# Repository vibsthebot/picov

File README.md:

# picov

A RP2040 powered Pico formfactor devboard using usb-c. It includes a 4x4 2020 neopixel array. The pcb was designed in KiCad.

## Schematic

## PCB

## PCB back art (designed in Figma!)

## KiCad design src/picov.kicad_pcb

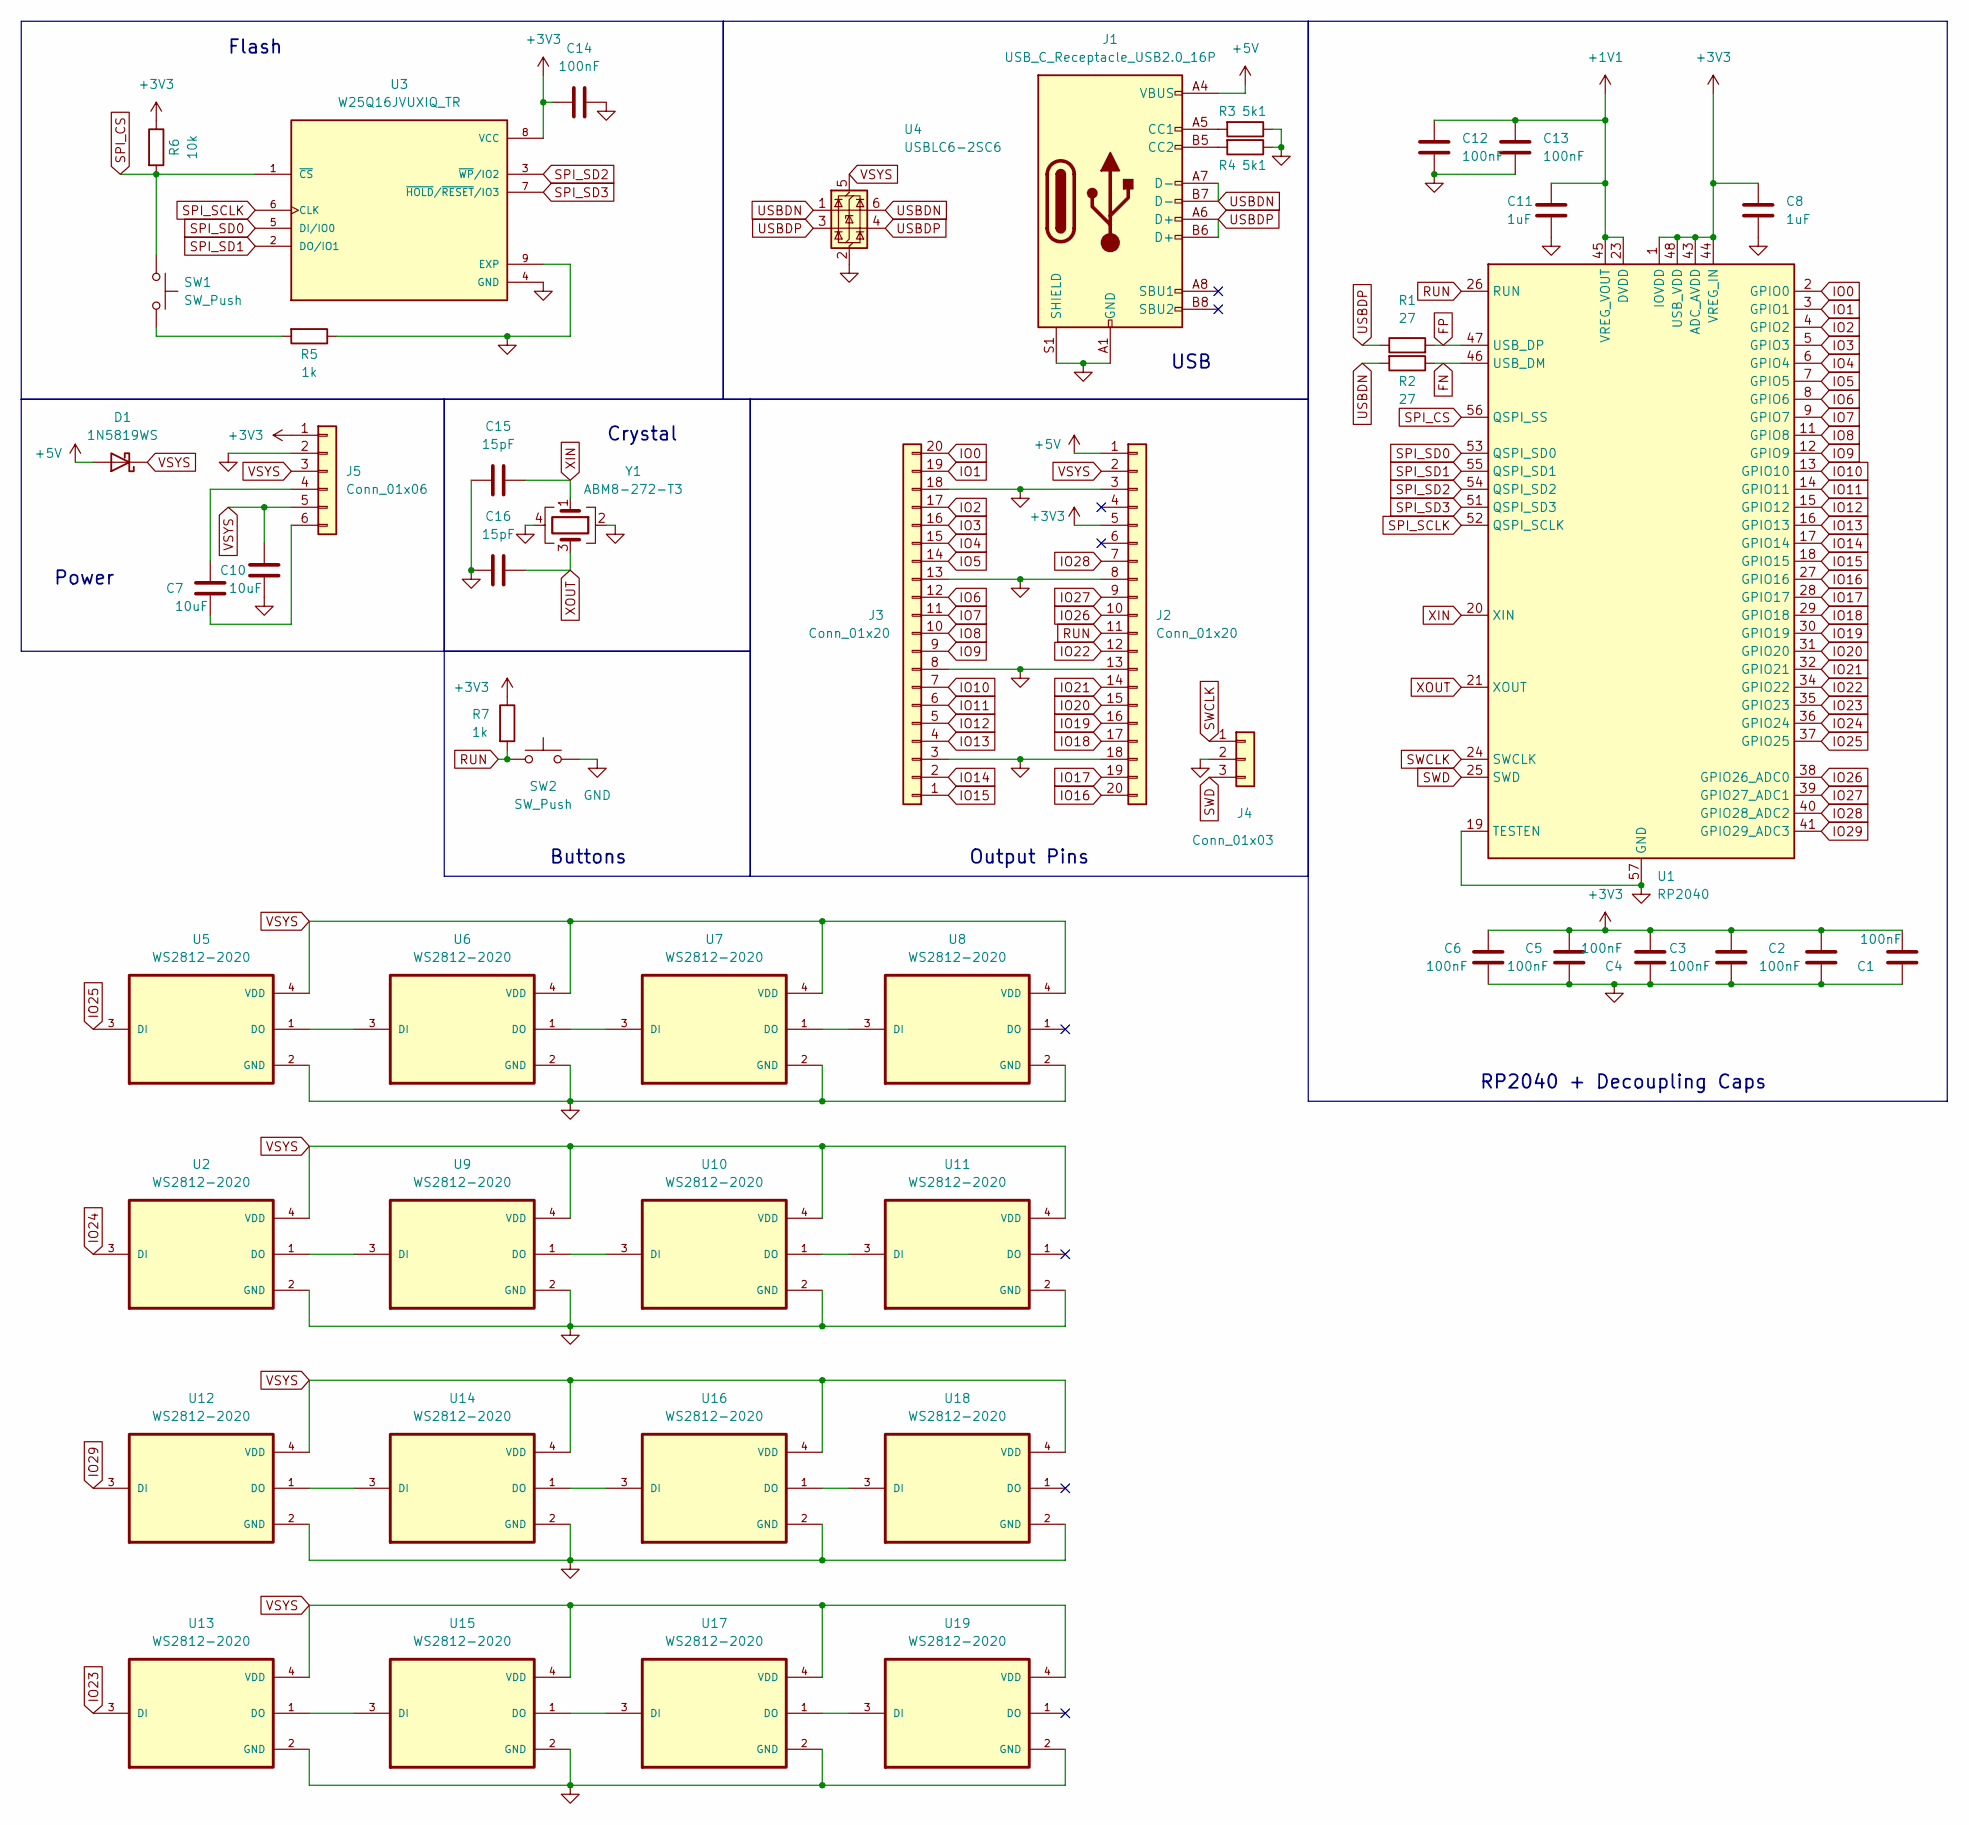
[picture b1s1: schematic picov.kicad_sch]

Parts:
C1, C2, C3, C4, C5, C6, C12, C13, C14: 100nF; C_0402_1005Metric; LCSC C1525
C7, C10: 10uF; C_0402_1005Metric; LCSC C15525
C8, C11: 1uF; C_0402_1005Metric; LCSC C52923
C15, C16: 15pF; C_0402_1005Metric; LCSC C1548
D1: 1N5819WS; D_SOD-123; LCSC C191023
J1: USB_C_Receptacle_USB2.0_16P; USB_C_Receptacle_G-Switch_GT-USB-7010ASV; LCSC C67380
J2, J3: Conn_01x20; PinHeader_1x20_P2.54mm_Vertical
J4: Conn_01x03; PinHeader_1x03_P2.54mm_Vertical
J5: Conn_01x06; SOT-23-6; LCSC C610271
R1, R2: 27; R_0402_1005Metric; LCSC C25100
R3, R4: 5k1; R_0402_1005Metric; LCSC C25905
R5, R7: 1k; R_0402_1005Metric; LCSC C11702
R6: 10k; R_0402_1005Metric; LCSC C25744
SW1, SW2: SW_Push; SMD_3x4; LCSC C455280
U1: RP2040; QFN-56-1EP_7x7mm_P0.4mm_EP3.2x3.2mm; LCSC C2040
U2, U5, U6, U7, U8, U9, U10, U11, U12, U13, U14, U15, U16, U17, U18, U19: WS2812-2020; LED_WS2812-2020; PARTREV V1.3; LCSC C26159668
U3: W25Q16JVUXIQ_TR; Winbond_USON-8-1EP_3x2mm_P0.5mm_EP0.2x1.6mm; PARTREV H; LCSC C2843335
U4: USBLC6-2SC6; SOT-23-6; LCSC C5180249
Y1: ABM8-272-T3; Crystal_SMD_3225-4Pin_3.2x2.5mm; LCSC C9002

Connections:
+1V1: C11.1, C12.1, C13.1, U1.23 (DVDD), U1.45 (VREG_VOUT), U1.50 (DVDD)
+3V3: C1.2, C2.2, C3.2, C4.2, C5.2, C6.2, C8.1, C14.1, J2.5, J5.1, R6.1, R7.1, U1.1 (IOVDD), U1.10 (IOVDD), U1.22 (IOVDD), U1.33 (IOVDD), U1.42 (IOVDD), U1.43 (ADC_AVDD), U1.44 (VREG_IN), U1.48 (USB_VDD), U1.49 (IOVDD), U3.8 (VCC)
+5V: D1.2 (A), J1.A4 (VBUS), J1.A9 (VBUS), J1.B4 (VBUS), J1.B9 (VBUS), J2.1
FN: R2.1, U1.46 (USB_DM)
FP: R1.2, U1.47 (USB_DP)
GND: C1.1, C2.1, C3.1, C4.1, C5.1, C6.1, C8.2, C10.2, C11.2, C12.2, C13.2, C14.2, C15.1, C16.1, J1.A1 (GND), J1.A12 (GND), J1.B1 (GND), J1.B12 (GND), J1.S1 (SHIELD), J2.3, J2.8, J2.13, J2.18, J3.3, J3.8, J3.13, J3.18, J4.2, J5.2, R3.1, R4.1, R5.1, SW2.2, U1.19 (TESTEN), U1.57 (GND), U2.2 (GND), U3.4 (GND), U3.9 (EXP), U4.2 (GND), U5.2 (GND), U6.2 (GND), U7.2 (GND), U8.2 (GND), U9.2 (GND), U10.2 (GND), U11.2 (GND), U12.2 (GND), U13.2 (GND), U14.2 (GND), U15.2 (GND), U16.2 (GND), U17.2 (GND), U18.2 (GND), U19.2 (GND), Y1.2, Y1.4
IO0: J3.20, U1.2 (GPIO0)
IO1: J3.19, U1.3 (GPIO1)
IO2: J3.17, U1.4 (GPIO2)
IO3: J3.16, U1.5 (GPIO3)
IO4: J3.15, U1.6 (GPIO4)
IO5: J3.14, U1.7 (GPIO5)
IO6: J3.12, U1.8 (GPIO6)
IO7: J3.11, U1.9 (GPIO7)
IO8: J3.10, U1.11 (GPIO8)
IO9: J3.9, U1.12 (GPIO9)
IO10: J3.7, U1.13 (GPIO10)
IO11: J3.6, U1.14 (GPIO11)
IO12: J3.5, U1.15 (GPIO12)
IO13: J3.4, U1.16 (GPIO13)
IO14: J3.2, U1.17 (GPIO14)
IO15: J3.1, U1.18 (GPIO15)
IO16: J2.20, U1.27 (GPIO16)
IO17: J2.19, U1.28 (GPIO17)
IO18: J2.17, U1.29 (GPIO18)
IO19: J2.16, U1.30 (GPIO19)
IO20: J2.15, U1.31 (GPIO20)
IO21: J2.14, U1.32 (GPIO21)
IO22: J2.12, U1.34 (GPIO22)
IO23: U1.35 (GPIO23), U13.3 (DI)
IO24: U1.36 (GPIO24), U2.3 (DI)
IO25: U1.37 (GPIO25), U5.3 (DI)
IO26: J2.10, U1.38 (GPIO26_ADC0)
IO27: J2.9, U1.39 (GPIO27_ADC1)
IO28: J2.7, U1.40 (GPIO28_ADC2)
IO29: U1.41 (GPIO29_ADC3), U12.3 (DI)
unnamed: J1.A5 (CC1), R3.2
unnamed: J1.B5 (CC2), R4.2
unnamed: C7.1, J5.4
unnamed: C7.2, J5.6
unnamed: R5.2, SW1.2
unnamed: U2.1 (DO), U9.3 (DI)
unnamed: U5.1 (DO), U6.3 (DI)
unnamed: U6.1 (DO), U7.3 (DI)
unnamed: U7.1 (DO), U8.3 (DI)
unnamed: U9.1 (DO), U10.3 (DI)
unnamed: U10.1 (DO), U11.3 (DI)
unnamed: U12.1 (DO), U14.3 (DI)
unnamed: U13.1 (DO), U15.3 (DI)
unnamed: U14.1 (DO), U16.3 (DI)
unnamed: U15.1 (DO), U17.3 (DI)
unnamed: U16.1 (DO), U18.3 (DI)
unnamed: U17.1 (DO), U19.3 (DI)
RUN: J2.11, R7.2, SW2.1, U1.26 (RUN)
SPI_CS: R6.2, SW1.1, U1.56 (QSPI_SS), U3.1 (~CS)
SPI_SCLK: U1.52 (QSPI_SCLK), U3.6 (CLK)
SPI_SD0: U1.53 (QSPI_SD0), U3.5 (DI/IO0)
SPI_SD1: U1.55 (QSPI_SD1), U3.2 (DO/IO1)
SPI_SD2: U1.54 (QSPI_SD2), U3.3 (~WP/IO2)
SPI_SD3: U1.51 (QSPI_SD3), U3.7 (~HOLD/~RESET/IO3)
SWCLK: J4.1, U1.24 (SWCLK)
SWD: J4.3, U1.25 (SWD)
USBDN: J1.A7 (D-), J1.B7 (D-), R2.2, U4.1 (I/O1), U4.6 (I/O1)
USBDP: J1.A6 (D+), J1.B6 (D+), R1.1, U4.3 (I/O2), U4.4 (I/O2)
VSYS: C10.1, D1.1 (K), J2.2, J5.3, J5.5, U2.4 (VDD), U4.5 (VBUS), U5.4 (VDD), U6.4 (VDD), U7.4 (VDD), U8.4 (VDD), U9.4 (VDD), U10.4 (VDD), U11.4 (VDD), U12.4 (VDD), U13.4 (VDD), U14.4 (VDD), U15.4 (VDD), U16.4 (VDD), U17.4 (VDD), U18.4 (VDD), U19.4 (VDD)
XIN: C15.2, U1.20 (XIN), Y1.1
XOUT: C16.2, U1.21 (XOUT), Y1.3

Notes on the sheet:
Buttons
Output Pins
Flash
Power
USB
RP2040 + Decoupling Caps
Crystal

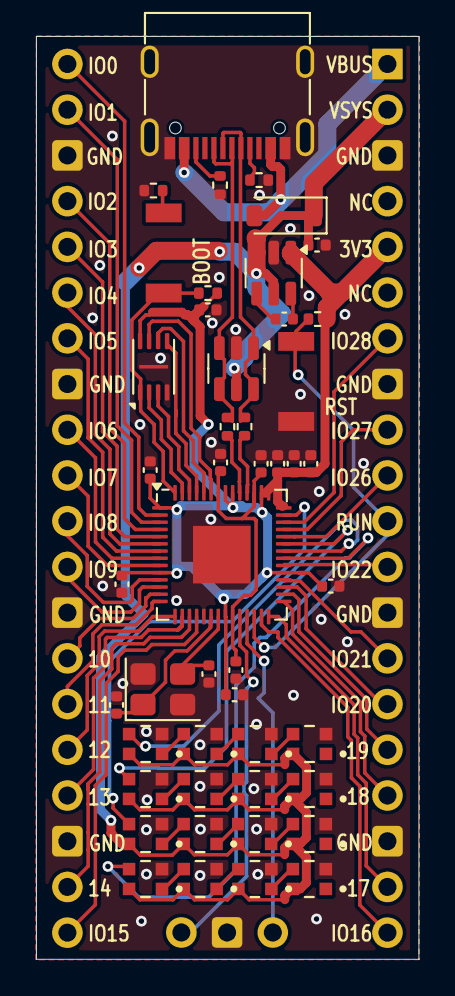
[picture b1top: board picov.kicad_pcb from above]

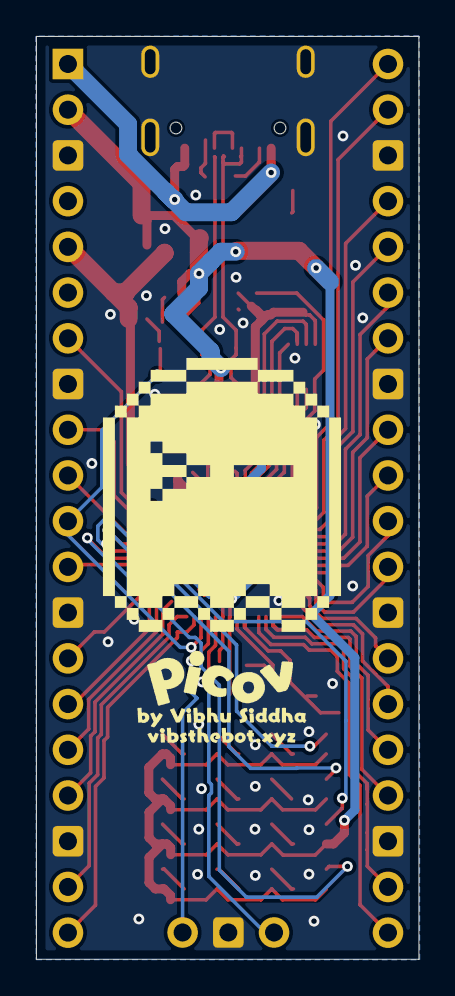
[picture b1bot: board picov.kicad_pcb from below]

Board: 2 copper layers, 21.2 x 51.3 mm, 50 parts (3 on the bottom side), 67 nets.

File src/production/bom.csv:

Designator,Footprint,Quantity,Value,LCSC Part #
"C1, C12, C13, C14, C2, C3, C4, C5, C6",0402,9,100nF,C1525
"C10, C7",0402,2,10uF,C15525
"C11, C8",0402,2,1uF,C52923
"C15, C16",0402,2,15pF,C1548
D1,D_SOD-123,1,1N5819WS,C191023
J1,USB_C_Receptacle_G-Switch_GT-USB-7010ASV,1,USB_C_Receptacle_USB2.0_16P,C67380
"J2, J3",PinHeader_1x20_P2.54mm_Vertical,2,Conn_01x20,
J4,PinHeader_1x03_P2.54mm_Vertical,1,Conn_01x03,
J5,SOT-23-6,1,Conn_01x06,C610271
"R1, R2",0402,2,27,C25100
"R3, R4",0402,2,5k1,C25905
"R5, R7",0402,2,1k,C11702
R6,0402,1,10k,C25744
"SW1, SW2",SMD_3x4,2,SW_Push,C455280
U1,QFN-56-1EP_7x7mm_P0.4mm_EP3.2x3.2mm,1,RP2040,C2040
"U10, U11, U12, U13, U14, U15, U16, U17, U18, U19, U2, U5, U6, U7, U8, U9",LED_WS2812-2020,16,WS2812-2020,C26159668
U3,Winbond_USON-8-1EP_3x2mm_P0.5mm_EP0.2x1.6mm,1,W25Q16JVUXIQ_TR,C2843335
U4,SOT-23-6,1,USBLC6-2SC6,C5180249
Y1,Crystal_SMD_3225-4Pin_3.2x2.5mm,1,ABM8-272-T3,C9002

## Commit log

2025-08-01 Got basic schematic done, need to add flash
2025-08-03 added castellated holes for sides, basic layout done
2025-08-10 Finished all design for the pcb
2025-08-17 finished pcb!
2025-08-17 cleaned up production files, finished readme
2025-08-17 removed castellated holes due to high jlcpcb pricing, finished 4x4 neopixel matrix
2025-08-18 changed some routing
